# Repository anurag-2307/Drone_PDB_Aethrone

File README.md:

# Drone_PDB_Aethrone

---

Candidate : Anurag Patankar

Personal Email : patankaranurag23@gmail.com

---

### Problem Statement :
Drone Power Distribution Board (PDB)

---
### Objective : 
Design a Power Distribution Board (PDB) for a medium-sized multirotor UAV capable of safely distributing power from a 6S LiPo battery to the avionics and propulsion systems.

## System Specifications

Input source - 6S LiPo battery, 18 V – 25.2 V (3.0–4.2 V/cell)
Continuous current - 80 A
Peak current - 120 A
Regulated outputs -	5 V @ 3 A, 12 V @ 2 A
Unregulated output  -	Battery voltage direct to ESC1–ESC4
PCB	2-layer, 3 oz copper (both outer layers)
Target thermal design margin - 20 °C rise above ambient
Input Connectors - XT60 (6S LiPo datasheet suggests XT90 for 80A continuous current, but the problem statement mentioned this, so I have used XT60 instead)
Output Connectors (Non-ESC) - JST
Output Connectors (ESC) - Solder holes

Note: Copper sizing is assumed to be at 3oz as it was not mentioned which size is to be used in the problem statement.

---

### Input Protection

1. Reverse Polarity Protection — U1 (LM74700) + Q1 (IPT015N10N5)

Rather than a series diode (which would waste power as heat at 80 A) , meaning 24–40 W burned continuously), the board uses an ideal diode controller driving an N-channel MOSFET, which behaves like a near-lossless diode.

U1 – TI LM74700-Q1: an ideal-diode controller rated for a 3.2 V–65 V supply range, covering the 18–25.2 V input. It drives an external NMOS and regulates its forward voltage drop to ~20 mV, versus the 300–500 mV of a real diode. It also blocks reverse current if the battery is momentarily disconnected/reconnected backward or during a fault, and responds in under 1 µs.
Q1 – Infineon IPT015N10N5: a 100 V, 300 A-rated N-channel MOSFET with a maximum Rds(on) of 1.5 mΩ. At 80 A continuous, conduction loss is I²R = 80² × 0.0015 ≈ 9.6 W; at 120 A peak, ≈21.6 W. The 300 A / 100 V rating gives sufficient margin over the operating envelope of 80 A/25.2 V. This MOSFET choice is what makes a lossless reverse polarity protection stage feasible at this current level, since a lower-current MOSFET would need paralleling.

---
2. TVS Diode

A unidirectional TVS Diode is placed across the protected rail to protect against voltage spikes. When the MOSFET turns off, it will create high voltage spikes (V = L. di/dt). To suppress this,  we use a bulk capacitor(s). E = $\frac{1}{2} \cdot L \cdot I$ and since the energy needs to be stored in the capacitor as well, $E = \frac{1}{2} \cdot C \cdot (V_{max}^2 - V_{nominal}^2)$. After some calculations, we get about C = 1666uF. To minimize the ESR, we place these in parallel instead of 1 big capacitor. Hence 680u * 3 = 2040uF.  

---
3. Fuse

Since we have to handle 120A (peak), the fuse needs to be a MIDI/MEGA style fuse. Since KiCAD doesn't have these footprints readily available, I created it myself with through-holes so that it can be soldered later on.

---
4. TPS5430, TPS5420 buck converters

We needed 5V@3A and 12V@2A, thus these buck converters were chosen after going through the datasheet. TPS5430 can provide a constant current of about 3A, while the TPS5420 can provide a constant current of 2A. 

Feedback Resistors calculation (TPS5430):
Vout = Vref × (1 + R2/R3)
5 V = 1.221 V × (1 + 10 kΩ / R3)
R3 = 10 kΩ / (5/1.221 − 1) ≈ 3.24 kΩ

(TPS5420):
12 V = 1.221 V × (1 + 10 kΩ / R5)
R5 = 10 kΩ / (12/1.221 − 1) ≈ 1.13 kΩ

---
5. Trace Width Calculation:

120 A peak (peak) at 3 oz for	20 °C rise (assuming) is about ~7917 mil²	≈ 48.6 mm which is massive. That is why I have used copper pour instead to dissipate heat evenly.
3A constant at 5V => 1 mm width. This is deliberately kept higher to reduce IR drop, and it also keeps output regulation tighter under load. 
2A constant at 12V => 1 mm width. Same reasoning as above. 

The standard used to calculate the trace widths is **IPC-2221**.

---
6. Via sizing
Via sizing basis: 0.8 mm drill / 1.2 mm pad, ≈4.8 A per via at 20 °C rise (1 oz barrel plating assumed). Thus for each ESC output, TVS diode GND, Bulk capacitor GND, 5 vias are placed and about 20 for Battery input ground pin. Default via sizes are used for all other components.

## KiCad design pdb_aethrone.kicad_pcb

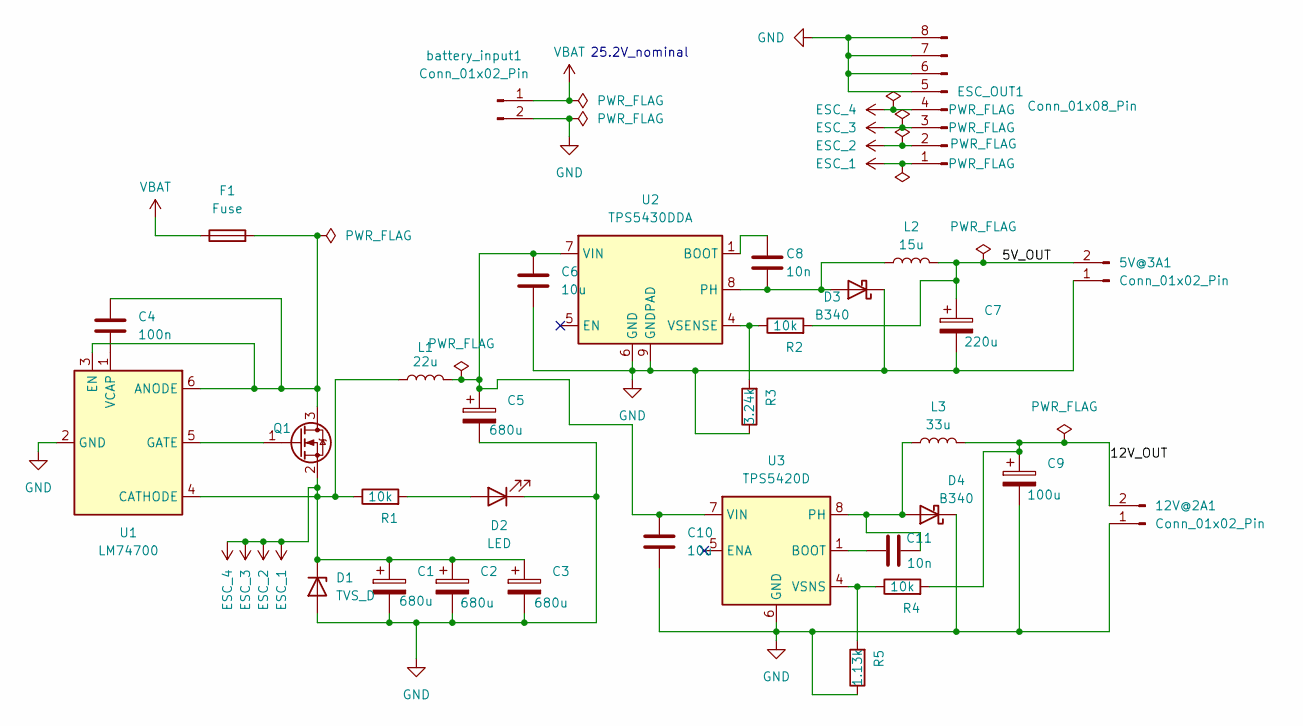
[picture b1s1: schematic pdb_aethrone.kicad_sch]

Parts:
5V@3A1, 12V@2A1: Conn_01x02_Pin; JST_XH_B2B-XH-A_1x02_P2.50mm_Vertical
C1, C2, C3, C5: 680u; CP_Radial_D10.0mm_P5.00mm
C4: 100n; C_0603_1608Metric
C6, C10: 10u; C_1210_3225Metric
C7: 220u; CP_Elec_6.3x7.7
C8, C11: 10n; C_0603_1608Metric
C9: 100u; CP_Elec_6.3x7.7
D1: TVS_D; D_SMC
D2: LED; LED_0805_2012Metric
D3, D4: B340; D_SMA
ESC_OUT1: Conn_01x08_Pin; ESC_Pins
F1: Fuse; Untitled
L1: 22u; L_12x12mm_H6mm
L2: 15u; L_12x12mm_H6mm
L3: 33u; L_12x12mm_H6mm
Q1: IPT015N10N5; Infineon_PG-HSOF-8-1
R1, R2, R4: 10k; R_0603_1608Metric
R3: 3.24k; R_0603_1608Metric
R5: 1.13k; R_0603_1608Metric
U1: LM74700; SOT-23-6
U2: TPS5430DDA; TI_SO-PowerPAD-8_ThermalVias
U3: TPS5420D; SOIC-8_3.9x4.9mm_P1.27mm
battery_input1: Conn_01x02_Pin; AMASS_XT60PW-F_1x02_P7.20mm_Horizontal

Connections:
/5V_OUT: 5V@3A1.2, C7.1, L2.2, R2.2
/12V_OUT: 12V@2A1.2, C9.1, L3.2, R4.2
ESC_1: C1.1, C2.1, C3.1, D1.1 (K), ESC_OUT1.1, ESC_OUT1.2, ESC_OUT1.3, ESC_OUT1.4, L1.1, Q1.2 (S), R1.1, U1.4 (CATHODE)
GND: 5V@3A1.1, 12V@2A1.1, C1.2, C2.2, C3.2, C5.2, C6.2, C7.2, C9.2, C10.2, D1.2 (A), D2.1 (K), D3.1 (K), D4.1 (K), ESC_OUT1.5, ESC_OUT1.6, ESC_OUT1.7, ESC_OUT1.8, R3.1, R5.1, U1.2 (GND), U2.6 (GND), U2.9 (GNDPAD), U3.6 (GND), battery_input1.2
unnamed: D2.2 (A), R1.2
unnamed: C8.2, D3.2 (A), L2.1, U2.8 (PH)
unnamed: C11.2, D4.2 (A), L3.1, U3.8 (PH)
unnamed: C4.1, F1.2, Q1.3 (D), U1.3 (EN), U1.6 (ANODE)
unnamed: Q1.1 (G), U1.5 (GATE)
unnamed: C4.2, U1.1 (VCAP)
unnamed: C8.1, U2.1 (BOOT)
unnamed: C5.1, C6.1, C10.1, L1.2, U2.7 (VIN), U3.7 (VIN)
unnamed: R2.1, R3.2, U2.4 (VSENSE)
unnamed: C11.1, U3.1 (BOOT)
unnamed: R4.1, R5.2, U3.4 (VSNS)
VBAT: F1.1, battery_input1.1

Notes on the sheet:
25.2V_nominal

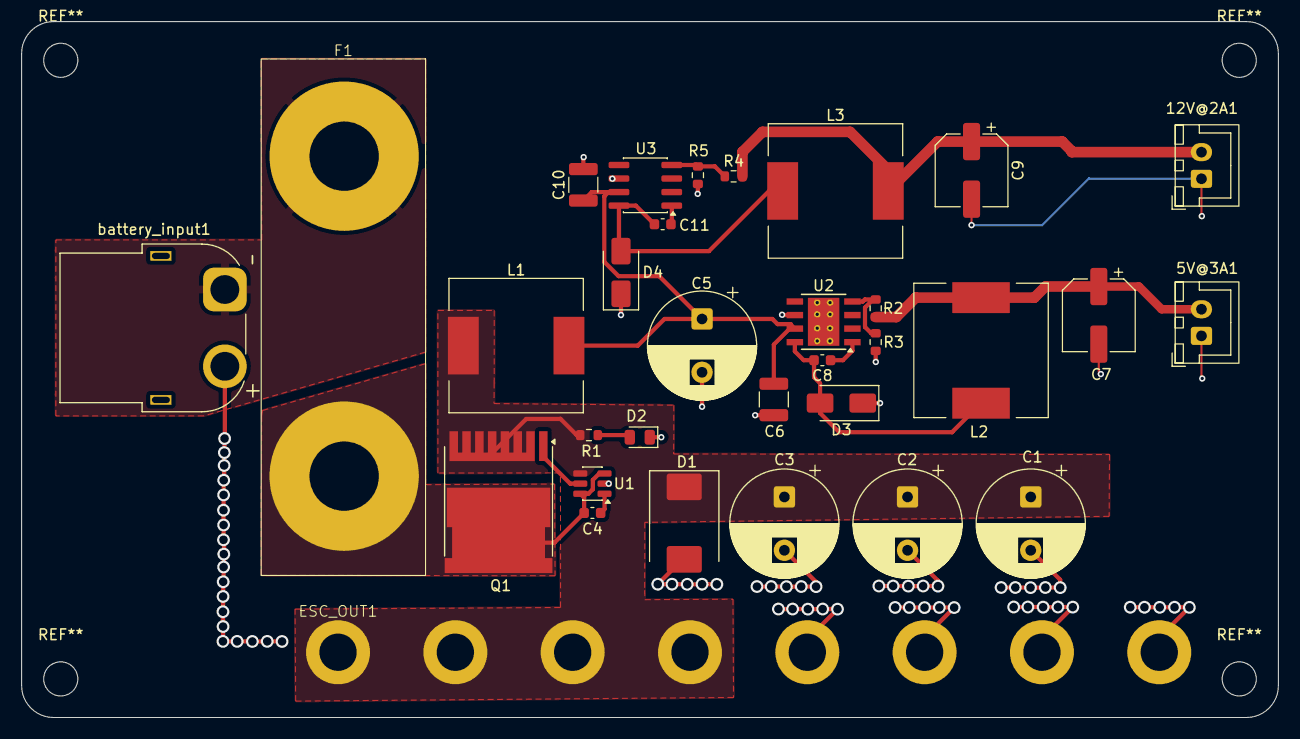
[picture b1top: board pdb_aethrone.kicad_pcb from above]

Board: 2 copper layers, 117.8 x 65.2 mm, 32 parts (0 on the bottom side), 16 nets.
